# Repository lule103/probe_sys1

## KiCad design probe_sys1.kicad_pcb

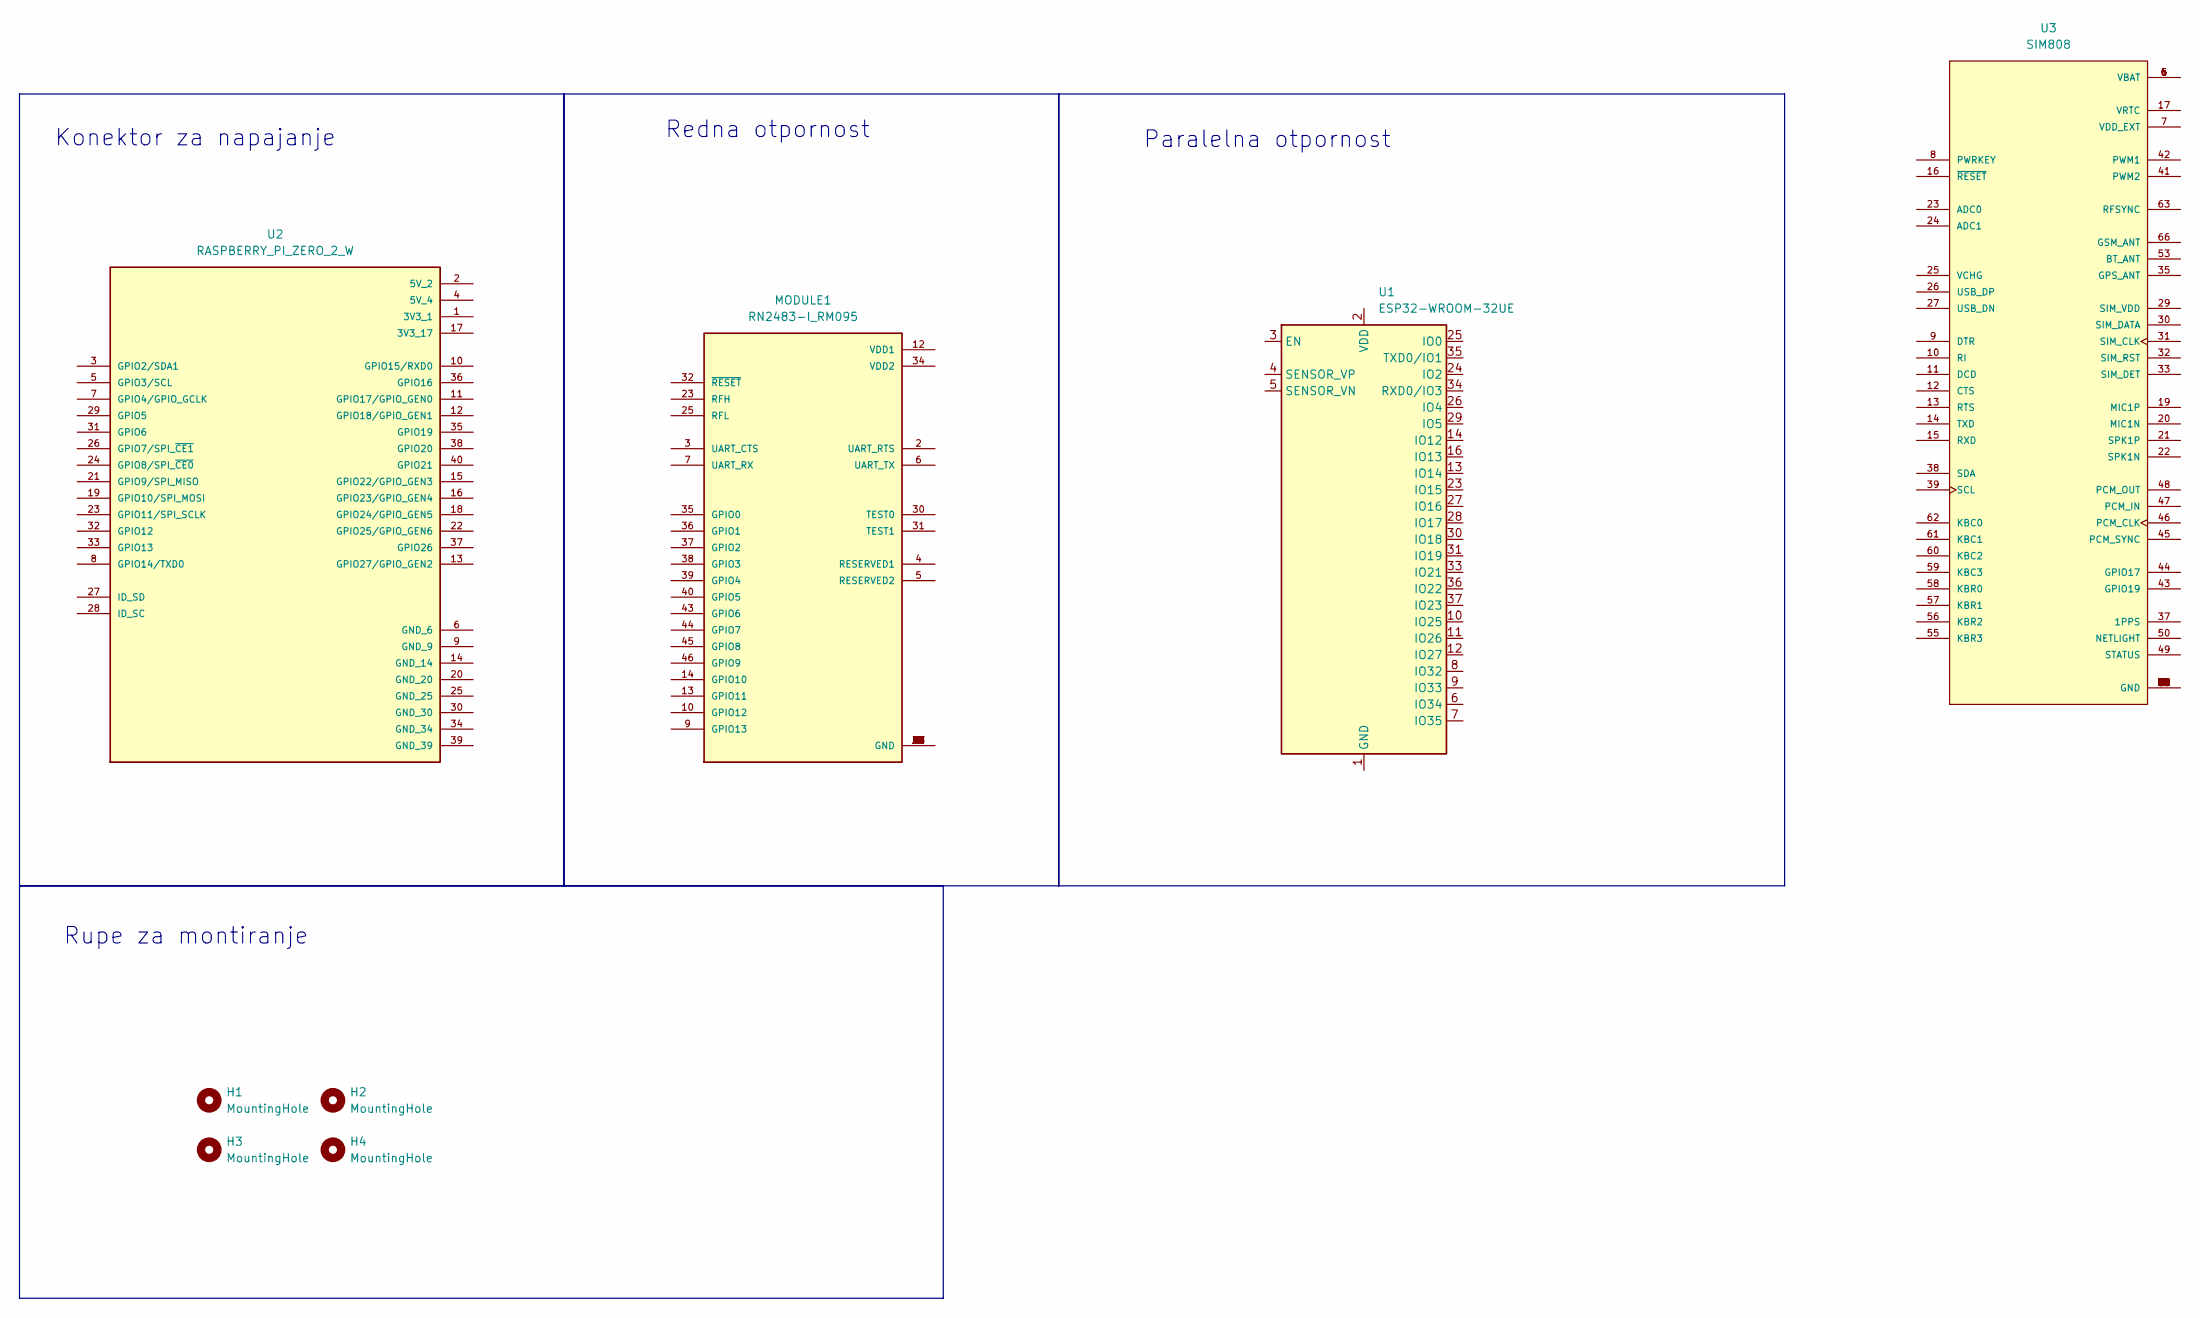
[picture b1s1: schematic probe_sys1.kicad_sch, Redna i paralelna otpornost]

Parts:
H1, H2, H3, H4: MountingHole; MountingHole_3.2mm_M3_ISO14580_Pad_TopBottom
MODULE1: RN2483-I_RM095
U1: ESP32-WROOM-32UE
U2: RASPBERRY_PI_ZERO_2_W; MODULE_RASPBERRY_PI_ZERO_2_W; PARTREV April 2024
U3: SIM808; PARTREV 1.03

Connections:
unnamed: MODULE1.1 (GND), MODULE1.8 (GND), MODULE1.11 (GND), MODULE1.20 (GND), MODULE1.21 (GND), MODULE1.22 (GND), MODULE1.24 (GND), MODULE1.26 (GND), MODULE1.27 (GND), MODULE1.28 (GND), MODULE1.33 (GND), MODULE1.41 (GND), MODULE1.47 (GND)
unnamed: U1.1 (GND), U1.15 (GND), U1.38 (GND), U1.39 (GND)
unnamed: U3.1 (GND), U3.2 (GND), U3.3 (GND), U3.18 (GND), U3.28 (GND), U3.34 (GND), U3.36 (GND), U3.40 (GND), U3.51 (GND), U3.52 (GND), U3.54 (GND), U3.64 (GND), U3.65 (GND), U3.67 (GND), U3.68 (GND)
unnamed: U3.4 (VBAT), U3.5 (VBAT), U3.6 (VBAT)

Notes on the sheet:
Konektor za napajanje
Rupe za montiranje
Paralelna otpornost
Redna otpornost

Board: 2 copper layers, 8 parts (0 on the bottom side), 4 nets, no tracks yet.

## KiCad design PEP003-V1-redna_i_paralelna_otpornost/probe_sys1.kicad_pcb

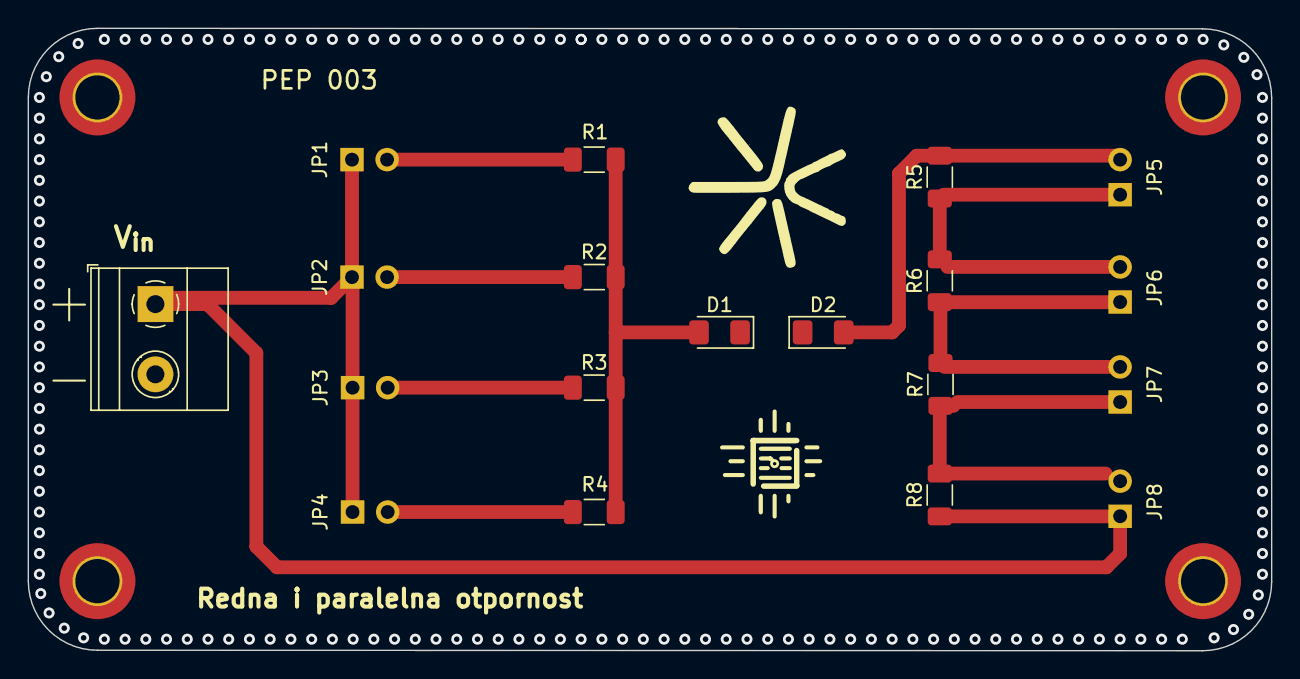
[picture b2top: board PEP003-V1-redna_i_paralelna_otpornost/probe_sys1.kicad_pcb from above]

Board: 2 copper layers, 90.0 x 45.0 mm, 23 parts (0 on the bottom side), 2 nets.

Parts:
D1, D2: LED; LED_1206_3216Metric_Pad1.42x1.75mm_HandSolder
H1, H2, H3, H4: MountingHole; MountingHole_3.2mm_M3_ISO14580_Pad_TopBottom
J2: Screw_Terminal_01x02; TerminalBlock_Phoenix_MKDS-1,5-2-5.08_1x02_P5.08mm_Horizont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
JP1, JP2, JP3, JP4, JP5, JP6, JP7, JP8: Jumper; PinHeader_1x02_P2.54mm_Vertical
R1, R4, R6: 4.7k; R_1206_3216Metric_Pad1.30x1.75mm_HandSolder
R2, R3, R8: 470; R_1206_3216Metric_Pad1.30x1.75mm_HandSolder
R5, R7: 47k; R_1206_3216Metric_Pad1.30x1.75mm_HandSolder

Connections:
0: D1.1 (K), D2.1 (K), J2.2
9V: J2.1, JP1.1 (A), JP2.1 (A), JP3.1 (A), JP4.1 (A), JP8.1 (A), R8.1

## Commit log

2025-07-04 init.
2025-07-04 RDM.
2025-07-04 RPI, RN, ESP.
2025-07-04 SIM, wroom.
2025-07-06 Started connecting IC pins
2025-07-06 Backup zip
